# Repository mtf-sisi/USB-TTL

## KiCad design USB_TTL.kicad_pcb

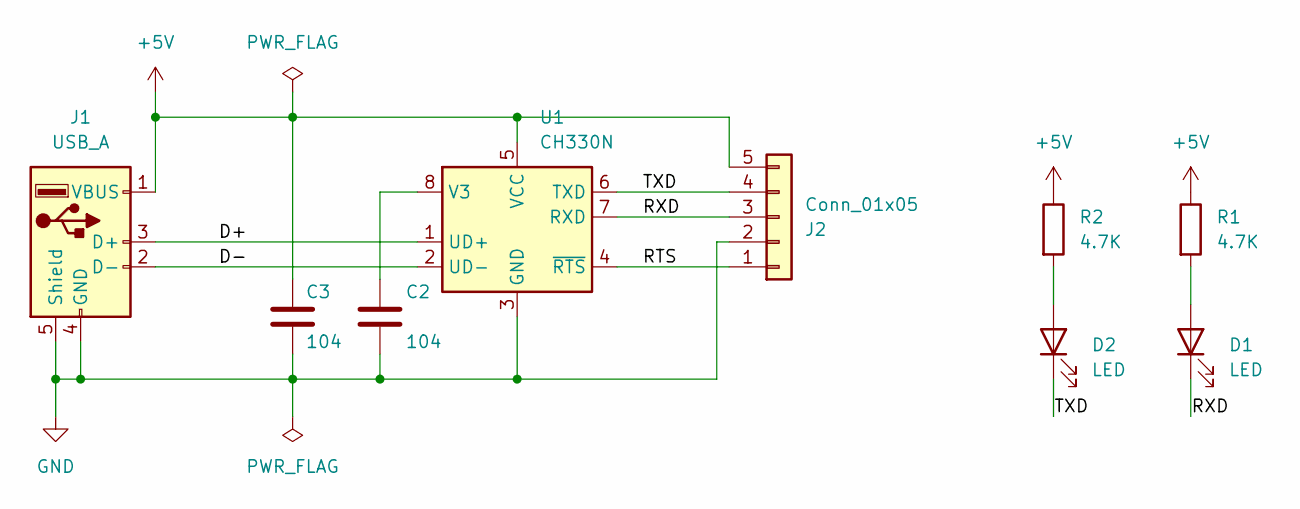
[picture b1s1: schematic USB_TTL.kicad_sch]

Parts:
C2, C3: 104; C_0201_0603Metric
D1, D2: LED; LED_0201_0603Metric
J1: USB_A; USB_A_CNCTech_1001-011-01101_Horizontal
J2: Conn_01x05; PinHeader_1x05_P2.54mm_Horizontal
R1, R2: 4.7K; R_0201_0603Metric
U1: CH330N; SOIC-8_3.9x4.9mm_P1.27mm

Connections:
+5V: C3.1, J1.1 (VBUS), J2.5, R1.1, R2.1, U1.5 (VCC)
/D+: J1.3 (D+), U1.1 (UD+)
/D-: J1.2 (D-), U1.2 (UD-)
/RTS: J2.1, U1.4 (~RTS)
/RXD: D1.1 (K), J2.3, U1.7 (RXD)
/TXD: D2.1 (K), J2.4, U1.6 (TXD)
GND: C2.2, C3.2, J1.4 (GND), J1.5 (Shield), J2.2, U1.3 (GND)
unnamed: D1.2 (A), R1.2
unnamed: D2.2 (A), R2.2
unnamed: C2.1, U1.8 (V3)

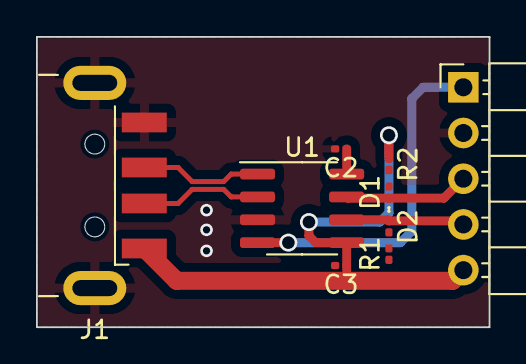
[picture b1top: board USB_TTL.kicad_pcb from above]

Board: 2 copper layers, 25.1 x 16.1 mm, 9 parts (0 on the bottom side), 10 nets.
